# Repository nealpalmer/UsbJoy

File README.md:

# UsbJoy
USB Joystick Controller 12Digital/SmartButton, 4Analog, 1Rotary, 1NeoPixel

This is a couple of circuit boards that make up a fancy USB joystick controller for FRC #2984.
It has both a HID joystick interface and a HID uart interface (for configuration) presented to the computer (i.e. it works in Windows and Linux).  No embedded programming experience is necessary to get it to work!  It also looks like just a HID analog joystick to Windows.

To add to this readme+files:
- mechanical drawing of the board (wid, hei, hole locations)
- photo of driver's panel
- update code when I'm done fiddling with stuff
- Add pictures where appropriate (pickit programming, USB programming cable)
- A description of how to get feedback from the robot to the leds.  Does this require a networktables application?  Or use Force-Feedback mechanisms?

# Features:
- 12 Digital inputs for buttons (3-pin White/Yellow/Green JST XH: 5V, signal with 10k pullup, GND)
  - 12 is probably enough buttons for a FRC operator panel.  We use 2x of these on the operator panel, and 1 on the driver panel.
  - simple buttons and switches can be used, just connect to the 'signal' and 'GND' pins of the 3-pin connector, and ignore the '5V' pin.
- 4 Analog inputs for joysticks or linear/rotary potentiometers (10k ohms) (3-pin Blue JST XH: 5V, signal with 100k+100k pullup+pulldown, GND).
  - 1 Analog [joystick](https://www.amazon.com/dp/B08CGYGMJL) for driving (X & Y)
  - 2 [linear potentiometers](https://www.amazon.com/dp/B07HNY7VWC) are useful for controlling speeds or small adjustments to some positioning
  - There are more analog input pins that could be used for more analog inputs, but that is left upto the user to figure out if they care.  But it is probably simpler/cheaper just to make more of these boards.
- 1 Digital input can be used to drive a NeoPixel string (be careful of 500mA fuse) (3-pin Yellow)
  - Can mimic the robots LEDs (in case you can't see the robot)
  - Can give you feedback as to some positioning (i.e. target is to the left/right or up/down, and by how much)
  - Can give you feedback as to if you are holding the playing piece.
- 4-pin JST XH rotary encoder for Z-axis (600 ppr*4phase = 2400/rev resolution assumed)
  - We use the rotary encoder to control the angle that the robot is pointing on the field.  Turn the rotary knob by 5degrees, and the robot also turns by 5degrees...
- 4or5 extra 'virtual' buttons, 1 toggling (optional), 4 as constants
  - 4 virtual constant buttons make it possible to distinguish between multiple controllers easily.
  - Multiple UsbJoy boards can be distinguished from each other from the FRC Robot software (just use those constant buttons).  This means we don't have to re-arrange the joystick order in driver station.
- Arduino Pro Micro USB-C 5V ATmega32U4 controller board used for ease of soldering.
  - Make sure to get one with the fuse on the TOP side of the board (i.e. no bottom side components).  [amazon.com](https://www.amazon.com/gp/product/B0B6HYLC44)
- SmartButton support for all 12 Digital inputs
  - You can choose what each button's LED looks like for informational purposes.
  - Flickering the button when initially pressed is simple feedback that the button should be working (commuincation to UsbJoy, LED works, button works, cable connected appropriately).
  - Having the button light up when it should be useable is useful (i.e. the playing piece is being held, you can now press the shoot button).
  - Have a couple of buttons light up to indicate the state of the robot.
- 4 Digital connectors (Green) can have their 5V power switched on/off for use with simple led outputs (SmartButton requires it to always be powered on).
  - This sounded like a great idea initially, but I don't see a use for it now...
- ESD diodes on all 16 3-pin connectors
- Configuration of SmartButton settings done through the USB-UART interface.
  - Some settings are saved in EEPROM (Neopixel length, LED starting value, joystick invert axis, ...) , some are temporary (LED current values, neopixel pattern).
  - The settings are stored in the UsbJoy's EEPROM, and are configured for that particular port.  The settings aren't saved in the SmartButton itself.
  - You could compile different firmware for each button, and fix each button's LED functionality that way.
- Programming of PIC micro-controller done over USB-UART with MCLRn button press required (don't have anything plugged into J8, J11, J12).
- Programming of SmartButton PIC micro-controller over USB-UART (use a custom cable from J8+J11+J12 to SmartButton 5-pin header).
- Colored JST-XH 3-pin connectors are available on [aliexpress.com](https://www.aliexpress.us/item/3256806937445015.html)
- Colored JST-XH terminal 3-pin connectors are available on [aliexpress.com](https://www.aliexpress.us/item/3256804014172692.html)
- pre-crimped 3-pin cables are available on [aliexpress.com](https://www.aliexpress.us/item/3256807213104605.html)  Just be aware that the pins have to be removed, and swapped so that it is a 1:1 cable instead of a 1:3 cable (or you are going to connect GND to 5V, and destroy your SmartButtons).
- pre-crimped 10-pin cables are available on [amazon.com](https://www.amazon.com/dp/B0B2RCW5JF) And you would have to replace the connectors with a 3-pin version (cheap, and comes from US, so comes quickly).

# UsbJoy Connector description
- 
- J1-J12 are the button inputs.  Pin 1: 5V (square pad), Pin 2: 'signal' (short to GND during button press), Pin 3: GND.
- J7-J10 (Green connectors) can have their 5V pin switched on/off if you want to use an LED directly connected instead of a SmartButton.  They have a 100ohm series resistor for the 5V output to limit it to about 25mA (plenty for a SmartButton).
- J12 can be setup to drive a neopixel string (a programmable strip of RGB leds).  Be aware that the max current for the string should be about 400mA, any higher and the 500mA USB fuse on the Pro Micro is likely to blow.  So for very long strings, external power should be provided for the array.
- J13-J16 are the analog inputs.  Pin 1: 5V, Pin 2: analog signal, Pin 3: GND.
- J17 is the encoder input.  Pin 1: 5V (square pad), Pin 2,3: A&B encoder inputs, Pin 4: GND.  Any AB encoder can be used.  The firmware is setup to make a reasonable output for a 600 pulse/revolution=2400 change/revolution encoder (i.e. Z-axis has a range of 0-2399).  You can change the 2400 limit to any other number in the code for both the Arduino and PIC to make a different resolution encoder look right.
- J8, J11, J12 are used for PIC programming (both the UsbJoy and SmartButton PIC).
- Button between J17 and J5 is the PIC MCLRn button that connects J8.signal to MCLRn so that it is possible to program the PIC.
- J18 (5-pin holes on back side) is the PIC ICSP header.  Connect the PICKIT5 here.  You must disconnect PICKIT5 for normal operation.

# Rotary Encoder
- Uses a simple 4-pin {5V,A,B,GND} [encoder](https://www.amazon.com/dp/B01MZ4V1XP)
- 600pulses/revolution * 4 edges per pulse = 2400 positions/revolution (about 1/6degree resolution)
- Returns 0-2399 as the Z-axis to the Joystick HID interface.

# SmartButton features
- About $1 for circuit board+cpu+connector.  About $2 per illuminated arcade button.
- Designed to solder directly to 30mm illuminated arcade buttons. [amazon EG-Starts Illuminated 30mm](https://www.amazon.com/EG-STARTS-Illuminated-Buttons-Raspberry/dp/B01N11BDX9) [Aliexpress 30mm](https://www.aliexpress.us/item/3256804217382377.html) [Coin/1P/2P](https://www.aliexpress.us/item/2251832825468632.html) [AutoRGB](https://www.aliexpress.us/item/3256805580977933.html) [50pack 28mm](https://www.aliexpress.us/item/3256805775007172.html) [Free ship $10](https://www.aliexpress.us/item/2251832849688596.html)
- NOTE: 24mm illuminated buttons don't work, the pins are too close together and the button binds when the board is connected (unless you pre-bend the pins).  And they are only 1mm smaller diameter for the nut, so no reason to use them.
- Other buttons could be used.  Just solder the switch pins to the button, and the LED pins to an LED+Resistor.
- 3-pin interface (5V, signal, GND)
- Some solder jumpers can be filled, and some jumpers cut to turn a smart button into a dumb button (i.e. no 5V present).
- State of the led_option is stored in UsbJoy, and associated with the port.  So the buttons don't have to store their operational state.
- Programming of pic16f15213 can be done with either PicKit5 or UsbJoy.
- LED options
  - 0: OFF
  - 1: ON
  - 2: ON for 100ms when button gets pressed
  - 3: ON while button is pressed
  - 4: FLASHING 100ms on/100ms off
  - 5: SIN()
  - 6: FLASHING while button is pressed
  - 7: Button toggles state each time it is pressed: LED lit when in 'pressed' state
  - 8: Button toggles state each time it is pressed: LED flashes when in 'pressed' state
  - 9: you can add more if you want...

# NeoPixel
- Uses an off-the-shelf neopixel array (WS2812B 5V leds) [Strip_of_leds](https://www.amazon.com/dp/B09PBHJG6G) [ring_of_leds](https://www.amazon.com/dp/B08GPWVD57)
- Takes over Digital input #11 (the Yellow connector)
- You are going to have to make a cable that has the JST XH connector on the end of it.
- You MUST pay attention to the current draw of the string.  The entire UsbJoy is limited to 500mA, and if you draw much more than that, the fuse will blow, and everything will stop working.  So make sure that the length of string can't draw too much power.
- Possibly add an external power connection to power the neopixel array.
- Color choices:
  - 0x00-0x3f: Black-to-White solid color choices (4 values per R,G,B)
  - 0x80-0xff: Single white LED on (can be set to match the rotary encoder)
  - Rainbow
  - Moving Rainbow

# Files included:
- UsbJoy_d12_a4_r-rev2/: Kicad layout files, and gerbers
- SmartButton-rev2/: Kicad layout files, and gerbers
- UsbJoy_bill_of_materials.csv: spreadsheets with all of the parts to purchase and quantities and ordering links, pcb, buttons, cables, other stuff...
- mechanics/: openscad & STL files for a couple of mounts for UsbJoy using the SmartButton, rotary dial, 
- software/SmartButton_firmware/:
- software/UsbJoy_firmware/: firmware for the Atmega32U4 microcontroller
- software/UsbJoy_pic_firmware/: firmware 
- software/program_pic/: small application to program the pic16f1778 on UsbJoy, and pic15f15213 on SmartButton

# Manufacturing suggestions:
- [oshpark.com](https://oshpark.com/) has wonderful pricing for qty3 of 2and4 layer boards and ships in 10 calendar days for almost everything (and you can pay more to get it earlier, or pay for faster shipping)
  - [UsbJoy_R2](https://oshpark.com/shared_projects/QPZCB1ZT) board order $20/3 boards
  - [SmartButton_R2](https://oshpark.com/shared_projects/OV1uAkH7) board order $1.70/3 boards ($6.80/12 boards)
- A 3d-printer can make the UsbJoy board attach directly to the screw threads of one of the buttons.  A couple of sample mount's source files are [here](https://makerworld.com/en/models/1602536-usbjoy-controller-mount-30mm-arcade-button).
- An 3d printed [encoder spring](https://makerworld.com/en/models/1602721-rotary-encoder-rotary-friction-spring) makes the encoder much better for not spinning the robot wildly.
- An [acrylic wheel](https://makerworld.com/en/models/1605249-encoder-finger-wheel) with finger holes for the encoder is very useful.
- Testing for button functionality can be done in windows with the built-in "USB game controllers"->properties window to see the buttons that get pressed. NEED A PICTURE HERE!
- You can extract a 3d model of the boards from kicad to use in your 3d cad system.  Kicad: File->Export->STEP
- digikey has all of the electrical components necessary (except for the LED and Arduino board).
- 3x UsbJoy parts kit
- 12x SmartButton parts kit
- The arduino pro micro has a 0.5A fuse on it.  The bottom side of the board will NOT be accessible.  If that 0.5A fuse is on the bottom side, and you have over current, then your boards will not be salvageable.  So get a version that has all the components on the top side.
- The discrete components are 0603 packages for easier soldering.
- Get some [illuminated magnifying glasses](https://www.amazon.com/YOCTOSUN-Magnifying-Rechargeable-1-5X-3-5X-Magnifier/dp/B0D8J3TYL3) for ease of soldering of small components. 
- Solder all of the SMT components before any thru-hole components.  Required for both boards, because some of the thru-hole soldering will make SMT parts unreachable.

# How to program Arduino Pro Micro's Atmega32U4 (the USB device):
- Run the [Arduino GUI](https://www.arduino.cc/en/software/) version 1.8.19 (or newer than May 2025).
- Load the *.ino file
- Set up the board to be "Arduino Leonardo".
- Plug in the board into USB, then select the right Com port in the Arduino GUI.
- "Upload" 
 from the Arduino GUI.
- Programming does not clear the EEPROM, so any settings should remain unaffected.

# How to program pic16f1778 on UsbJoy using PICKIT5 programmer:
- Disconnect the last 2 buttons (Yellow and white next to each other)
- type "q1" on the uart to disable the 7,10,11 button communications
- Run the [Microchip IDE](https://www.microchip.com/en-us/tools-resources/develop/mplab-x-ide)
- Load the project
- Compile the project for production
- Use one of the current PIC programmers (pickit5 is probably preferred), and plug it into the 5-pin holes on the bottom side of the board.  And have the IDE program the device.
- type "q0" on the uart to re-enable the last 2 button functionality
# How to program pic16f1778 on UsbJoy using UsbJoy's USB connection:
- Disconnect buttons 7,10,11 (Green, White, Yellow) - they will interfere with the programming.
- Connect UsbJoy to the Windows PC.
- Figure out what com port (use Windows Device Manager) UsbJoy is using.
- Run "program_pic.exe usbjoy [filename].hex COM[#]"
- Press and hold the button next to the rotary connector for the full programming time (about 15 seconds).  If you forget this step, then you will receive a message "Error: couldn't find expected PIC CPU".
- Wait for programming to complete.
- Release the button.
- You can now reconnect the disconnected buttons.

# How to program pic16f15213 on SmartButton using PICKIT5:
- Run the [Microchip IDE](https://www.microchip.com/en-us/tools-resources/develop/mplab-x-ide)
- Load the project
- Compile the project for production
- Make sure the SmartButton isn't pressed, Connect the 3-pin cable to the UsbJoy (for 5V power), plug the pickit5 into the 5-pin holes on the SmartButton board.  And have the IDE program the device.
# How to program pic16f15213 on SmartButton using UsbJoy's USB interface:
- Connect 3+3+3pin cable ends into UsbJoy (match yellow J12,white J11,green J8 connectors), connect 5-pin cable end into SmartButton.
- Run "program_pic sb smartbutton.hex COM[#]".
- Quick Test: While plugged into the 5-pin cable, you should see the led in the button flicker VERY VERY dim.
- Quick Test: While plugged into the 5-pin cable, if you press the button, the LED should light up.
- You will need to create a cable to connect J8,J11,J12 to a 5-pin header.  It is probably easiest and more reliable to make an 3+3+3-pin to 5-pin XH only cable, and then solder the B5B-XH header to a 0.1" header.
 - pin1: MCLRn -> Red/Green/J8.2
 - pin2: 5V -> White/White/J11.1
 - pin3: GND -> Blue/Yellow/J12.3
 - pin4: PGD -> Blue/Yellow/J12.2
 - pin5: PGC -> White/White/J11.2
 - 
 - 

# How to initially configure UsbJoy:
- Connect USB to a PC.
- Open a terminal program (I like [MobaXterm](https://mobaxterm.mobatek.net/)), and connect to the correct com port (use windows device manager, and find the 'leonardo' port listed) (linux: 'dmesg' to find the correct '/dev/ttyUSB#' when you plug into USB).
- Any baud rate is fine, because it is a virtual serial port.
- 'h'+enter to get the help menu
- All settings commands are "letter+hex_number+enter".
- Important EEPROM settings to run:
  - 'u#" to set the upper 4 bits for the virtual buttons to uniquely identify this particular board (saved to EEPROM)
  - "m#val" to set the SmartLed DEFAULT setting for that port (not for the SmartLed itself) to the desired LED pattern (and toggle functionality) (saved to EEPROM)
  - "n#" to set the number of neopixel leds in the string - set to "n0" to indicate that there isn't a neopixel string.
  - "v#" to set the power-on setting for the Green ports - probably want them always on "vF" unless they are being used in some interesting way.
  - "V#" to set the power-on DEFAULT for the Green ports (saved to EEPROM)

# Future enhancements
- Add a 5-pin direct programming header for connecting to SmartButton (no need for weird programming cable).
- Move QR code to top side of board.
- UsbJoy Rev3: 4-pin header, 1 button signal, 1 led signal, no CPU on button side for LED functionality.  Still compatible with smart buttons after making a 4-pin to 3-pin cable.
- Dumbutton30mm: 4-pin header - nothing else (no cap, no res, no CPU).

# History of major changes
- 10/1/2025: Added an option for dumb buttons - fixes contention on the signal pin, and fixes spurious phantom button presses when using simple buttons.
- 8/8/2025: Added RZ axis to have the full resolution of the 2400/rev encoder when used with FRC DriverStation that only has 200 values per axis.
- 7/16/2025: Added MPLAB project files.
- 7/16/2025: SmartButton pic programming working over USB
- 7/16/2025: Added PDF of schematics.
- 7/15/2025: Uploaded 3d and lasercut objects to makerworld.com

Neal Palmer,
**FRC team #2984 Vikings Robotics,**
La Jolla, CA, USA

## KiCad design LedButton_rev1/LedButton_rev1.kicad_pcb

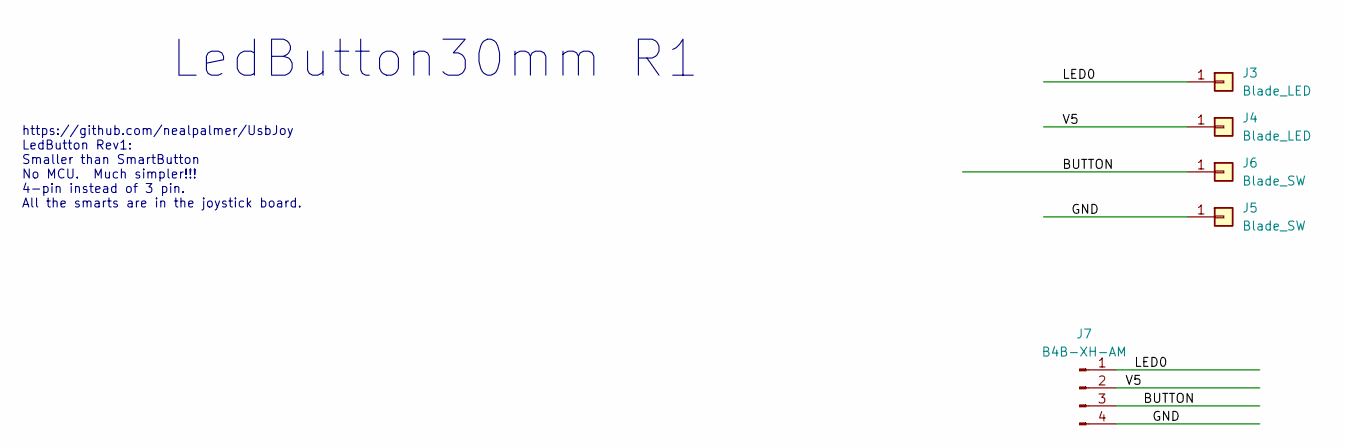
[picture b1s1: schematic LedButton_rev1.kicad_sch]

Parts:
J3, J4: Blade_LED; blade_3.75x1
J5, J6: Blade_SW; blade_3.75x1
J7: B4B-XH-AM; JST_XH_B4B-XH-AM_1x04_P2.50mm_Vertical

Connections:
/BUTTON: J6.1, J7.3
/GND: J5.1, J7.4
/LED0: J3.1, J7.1
/V5: J4.1, J7.2

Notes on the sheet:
https://github.com/nealpalmer/UsbJoy LedButton Rev1: Smaller than SmartButton No MCU. Much simpler!!! 4-pin instead of 3 pin. All the smarts are in the joystick board.
LedButton30mm R1

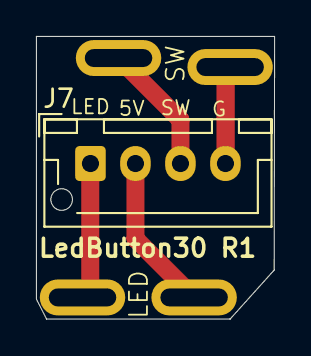
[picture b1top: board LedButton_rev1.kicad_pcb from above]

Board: 2 copper layers, 13.2 x 15.7 mm, 5 parts (0 on the bottom side), 4 nets.

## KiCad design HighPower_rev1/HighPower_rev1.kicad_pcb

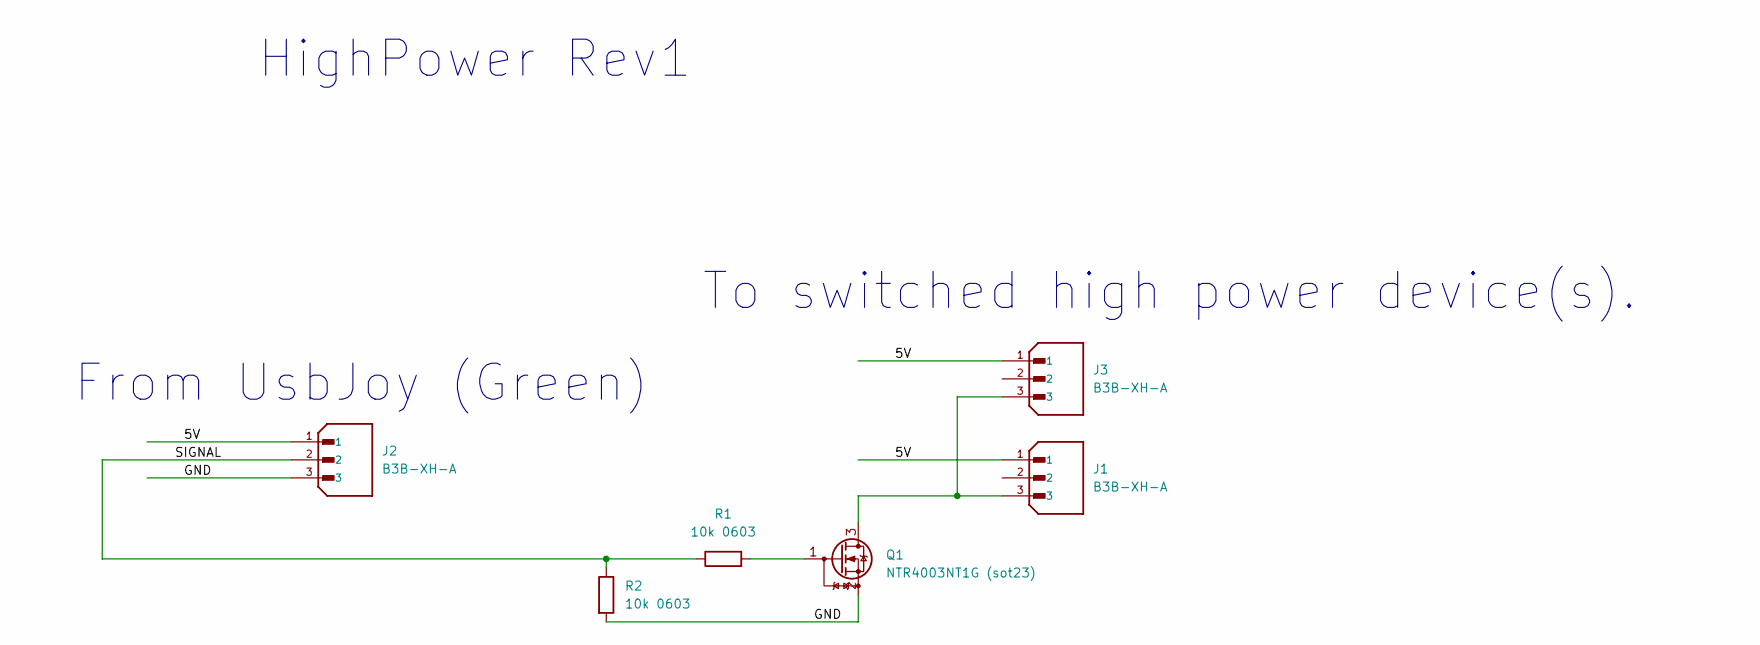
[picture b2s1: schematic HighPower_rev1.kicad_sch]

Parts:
J1, J2, J3: B3B-XH-A; JST_XH_B3B-XH-A_1x03_P2.50mm_Vertical; PARTREV 7/4/21
Q1: NTR4003NT1G (sot23); SOT-23
R1, R2: 10k 0603; C_0603_1608Metric_Pad1.08x0.95mm_HandSolder

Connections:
/5V: J1.1, J2.1, J3.1
/GND: J2.3, Q1.2 (S), R2.2
/SIGNAL: J2.2, R1.1, R2.1
unnamed: J1.3, J3.3, Q1.3 (D)
unnamed: Q1.1 (G), R1.2

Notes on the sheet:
HighPower Rev1
From UsbJoy (Green)
To switched high power device(s).

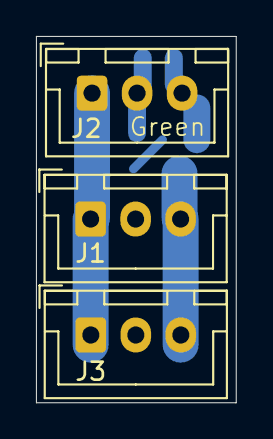
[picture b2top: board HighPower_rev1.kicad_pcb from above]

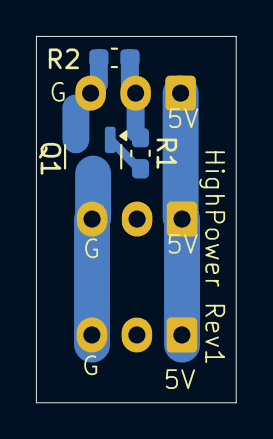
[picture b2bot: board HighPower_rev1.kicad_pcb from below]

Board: 2 copper layers, 11.1 x 20.4 mm, 6 parts (3 on the bottom side), 5 nets.

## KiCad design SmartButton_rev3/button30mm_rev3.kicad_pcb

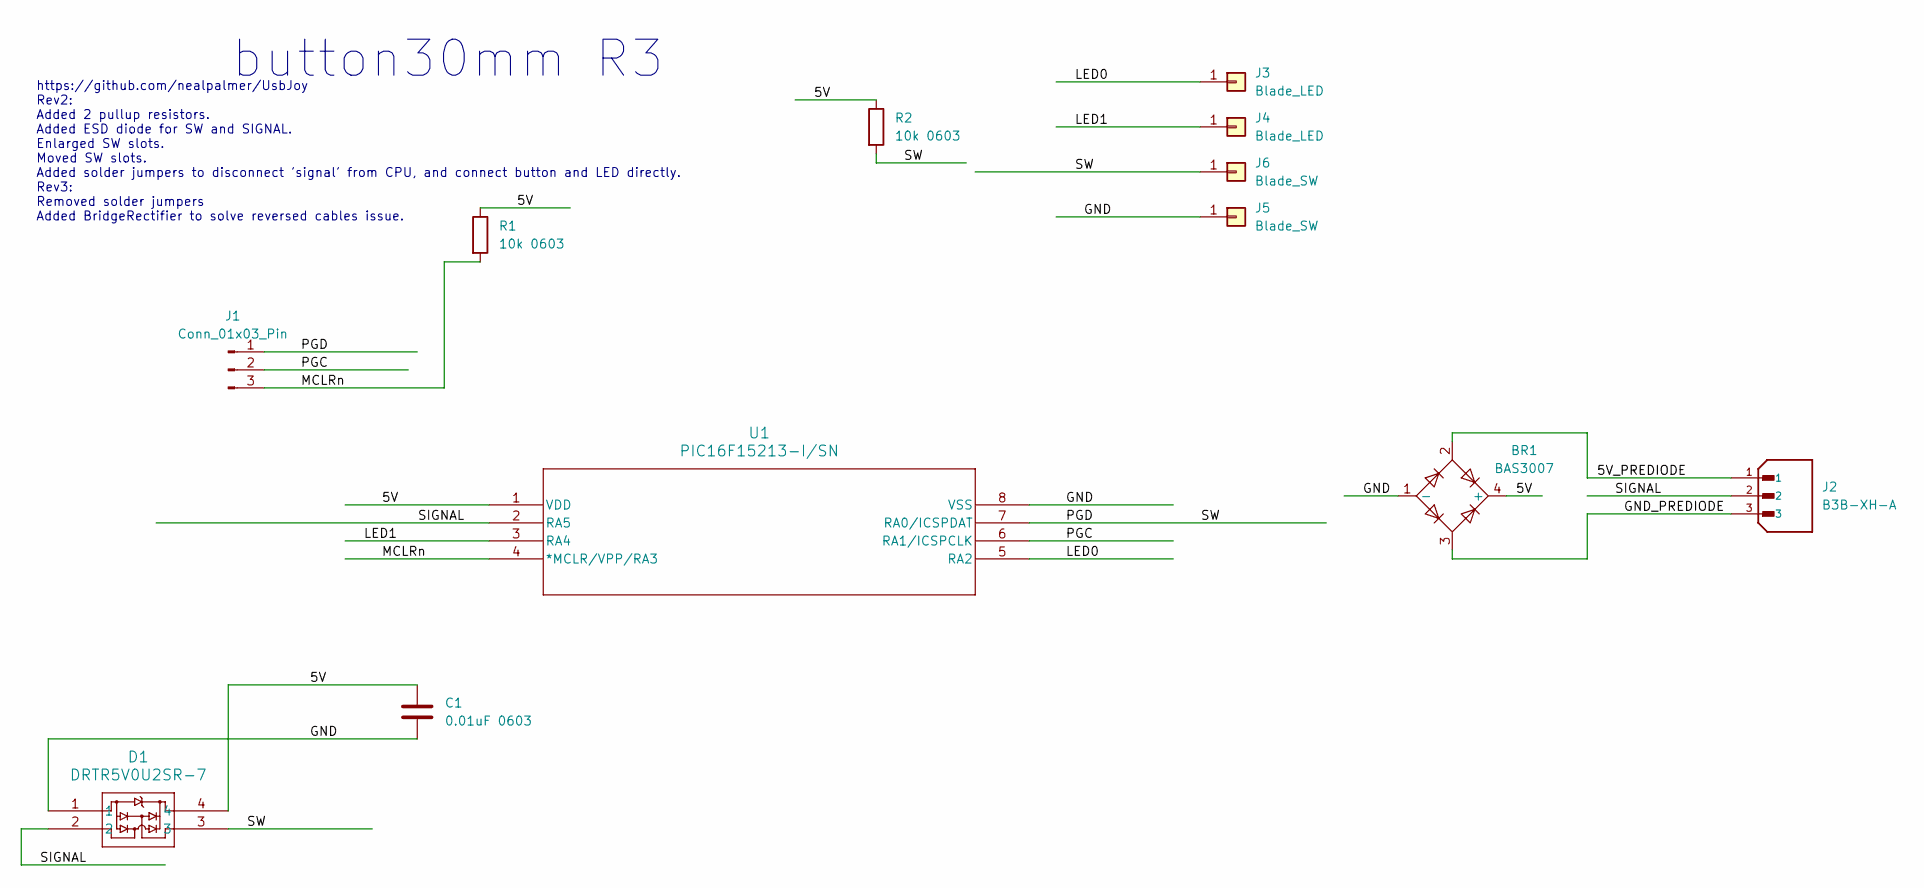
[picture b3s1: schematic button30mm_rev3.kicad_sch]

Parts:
BR1: BAS3007; SOT143_DIO
C1: 0.01uF 0603; C_0603_1608Metric_Pad1.08x0.95mm_HandSolder
D1: DRTR5V0U2SR-7; SOT143_DIO
J1: Conn_01x03_Pin; PinHeader_1x03_P2.54mm_Vertical
J2: B3B-XH-A; JST_XH_B3B-XH-A_1x03_P2.50mm_Vertical; PARTREV 7/4/21
J3, J4: Blade_LED; blade_3.75x1
J5, J6: Blade_SW; blade_3.75x1
R1, R2: 10k 0603; C_0603_1608Metric_Pad1.08x0.95mm_HandSolder
U1: PIC16F15213-I/SN; SOIC-8_3.9x4.9mm_P1.27mm

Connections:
/5V: BR1.4 (+), C1.1, D1.4, R1.1, R2.1, U1.1 (VDD)
/5V_PREDIODE: BR1.2, J2.1
/GND: BR1.1 (-), C1.2, D1.1, J5.1, U1.8 (VSS)
/GND_PREDIODE: BR1.3, J2.3
/LED0: J3.1, U1.5 (RA2)
/LED1: J4.1, U1.3 (RA4)
/MCLRn: J1.3, R1.2, U1.4 (*MCLR/VPP/RA3)
/PGC: J1.2, U1.6 (RA1/ICSPCLK)
/PGD: D1.3, J1.1, J6.1, R2.2, U1.7 (RA0/ICSPDAT)
/SIGNAL: D1.2, J2.2, U1.2 (RA5)

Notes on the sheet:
https://github.com/nealpalmer/UsbJoy Rev2: Added 2 pullup resistors. Added ESD diode for SW and SIGNAL. Enlarged SW slots. Moved SW slots. Added solder jumpers to disconnect 'signal' from CPU, and connect button and LED directly. Rev3: Removed solder jumpers Added BridgeRectifier to solve reversed 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
button30mm R3

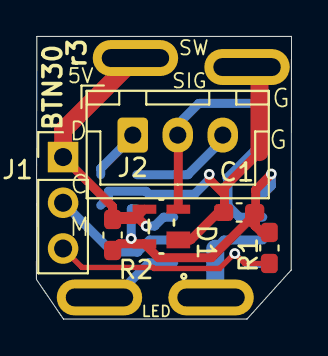
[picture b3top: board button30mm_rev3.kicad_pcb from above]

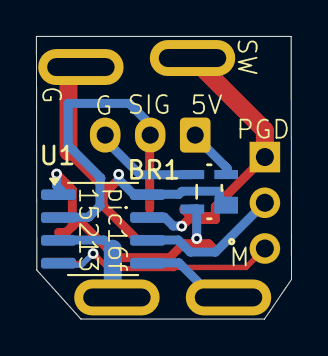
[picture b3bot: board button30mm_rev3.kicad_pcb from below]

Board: 2 copper layers, 14.2 x 15.7 mm, 12 parts (2 on the bottom side), 10 nets.

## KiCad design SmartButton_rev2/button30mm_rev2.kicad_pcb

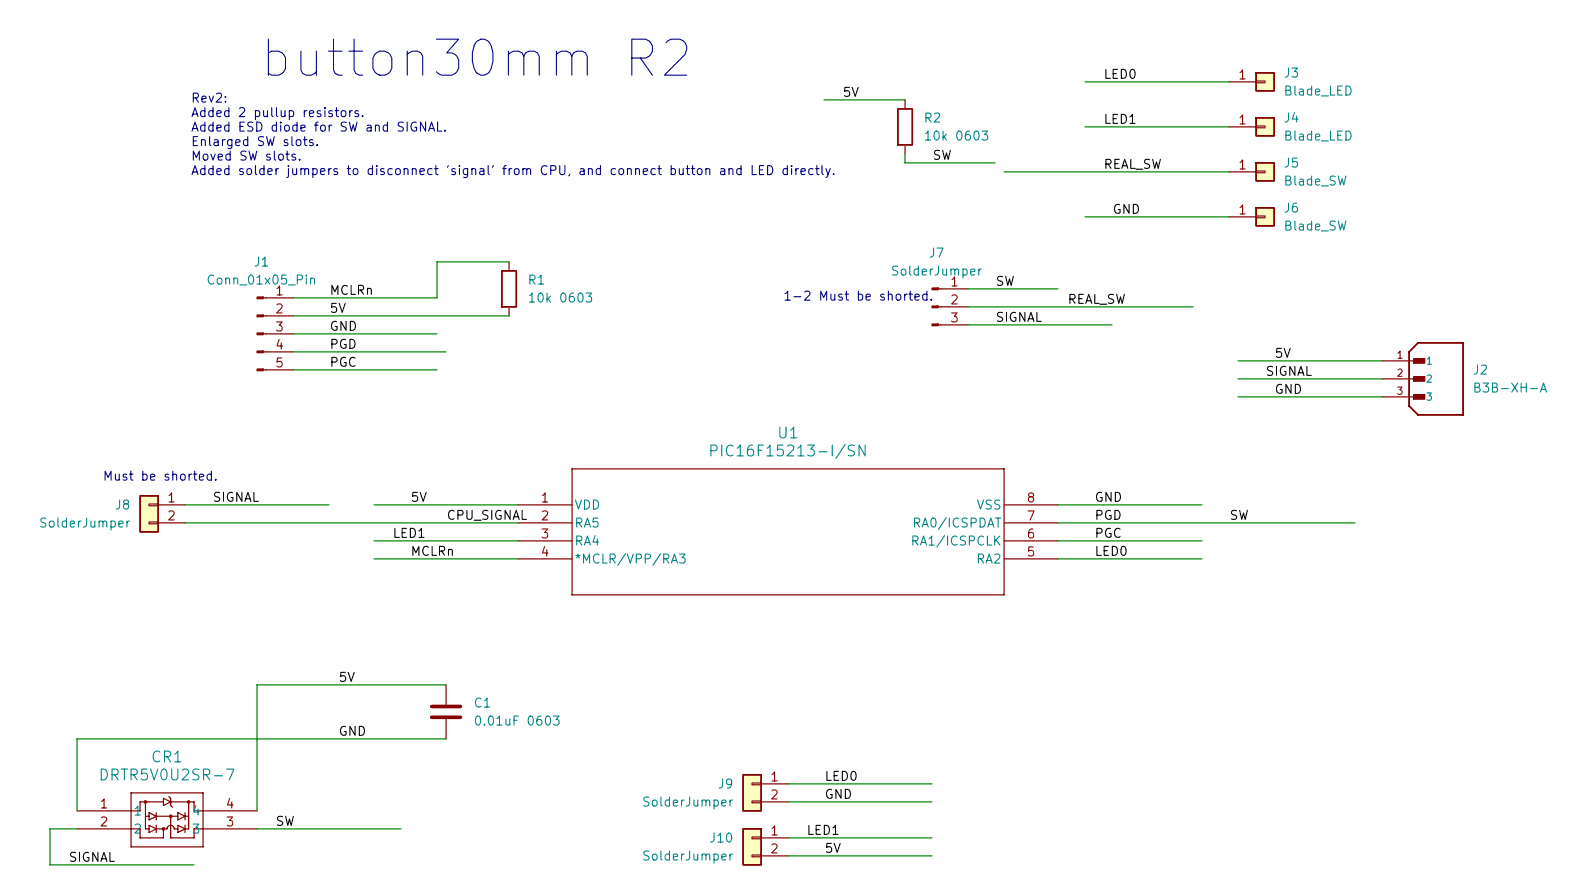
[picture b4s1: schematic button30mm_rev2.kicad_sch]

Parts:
C1: 0.01uF 0603; C_0603_1608Metric_Pad1.08x0.95mm_HandSolder
CR1: DRTR5V0U2SR-7; SOT143_DIO
J1: Conn_01x05_Pin; PinHeader_1x05_P2.54mm_Vertical
J2: B3B-XH-A; JST_XH_B3B-XH-A_1x03_P2.50mm_Vertical; PARTREV 7/4/21
J3, J4: Blade_LED; blade_3.75x1
J5, J6: Blade_SW; blade_3.75x1
J7: SolderJumper; SolderJumper-3_P1.3mm_Shorted_Pad0.8x0.4mm
J8: SolderJumper; SolderJumper-2_P1.3mm_Shorted_Pad0.4x0.8mm
J9, J10: SolderJumper; SolderJumper-2_P1.3mm_Open_Pad0.4x0.8mm
R1, R2: 10k 0603; C_0603_1608Metric_Pad1.08x0.95mm_HandSolder
U1: PIC16F15213-I/SN; SOIC-8_5.3x5.3mm_P1.27mm

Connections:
/5V: C1.1, CR1.4, J1.2, J2.1, J10.2, R1.2, R2.1, U1.1 (VDD)
/CPU_SIGNAL: J8.2, U1.2 (RA5)
/GND: C1.2, CR1.1, J1.3, J2.3, J6.1, J9.2, U1.8 (VSS)
/LED0: J3.1, J9.1, U1.5 (RA2)
/LED1: J4.1, J10.1, U1.3 (RA4)
/MCLRn: J1.1, R1.1, U1.4 (*MCLR/VPP/RA3)
/PGC: J1.5, U1.6 (RA1/ICSPCLK)
/PGD: CR1.3, J1.4, J7.1, R2.2, U1.7 (RA0/ICSPDAT)
/REAL_SW: J5.1, J7.2
/SIGNAL: CR1.2, J2.2, J7.3, J8.1

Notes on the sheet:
Must be shorted.
Rev2: Added 2 pullup resistors. Added ESD diode for SW and SIGNAL. Enlarged SW slots. Moved SW slots. Added solder jumpers to disconnect 'signal' from CPU, and connect button and LED directly.
button30mm R2
1-2 Must be shorted.

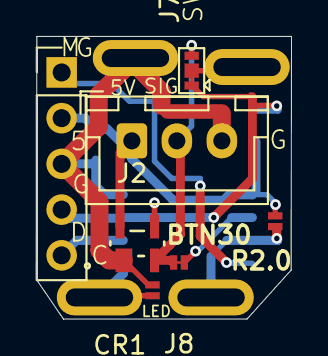
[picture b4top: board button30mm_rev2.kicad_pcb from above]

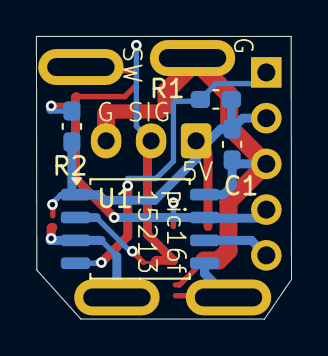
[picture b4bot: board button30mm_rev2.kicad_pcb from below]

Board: 2 copper layers, 14.2 x 15.7 mm, 15 parts (4 on the bottom side), 10 nets.

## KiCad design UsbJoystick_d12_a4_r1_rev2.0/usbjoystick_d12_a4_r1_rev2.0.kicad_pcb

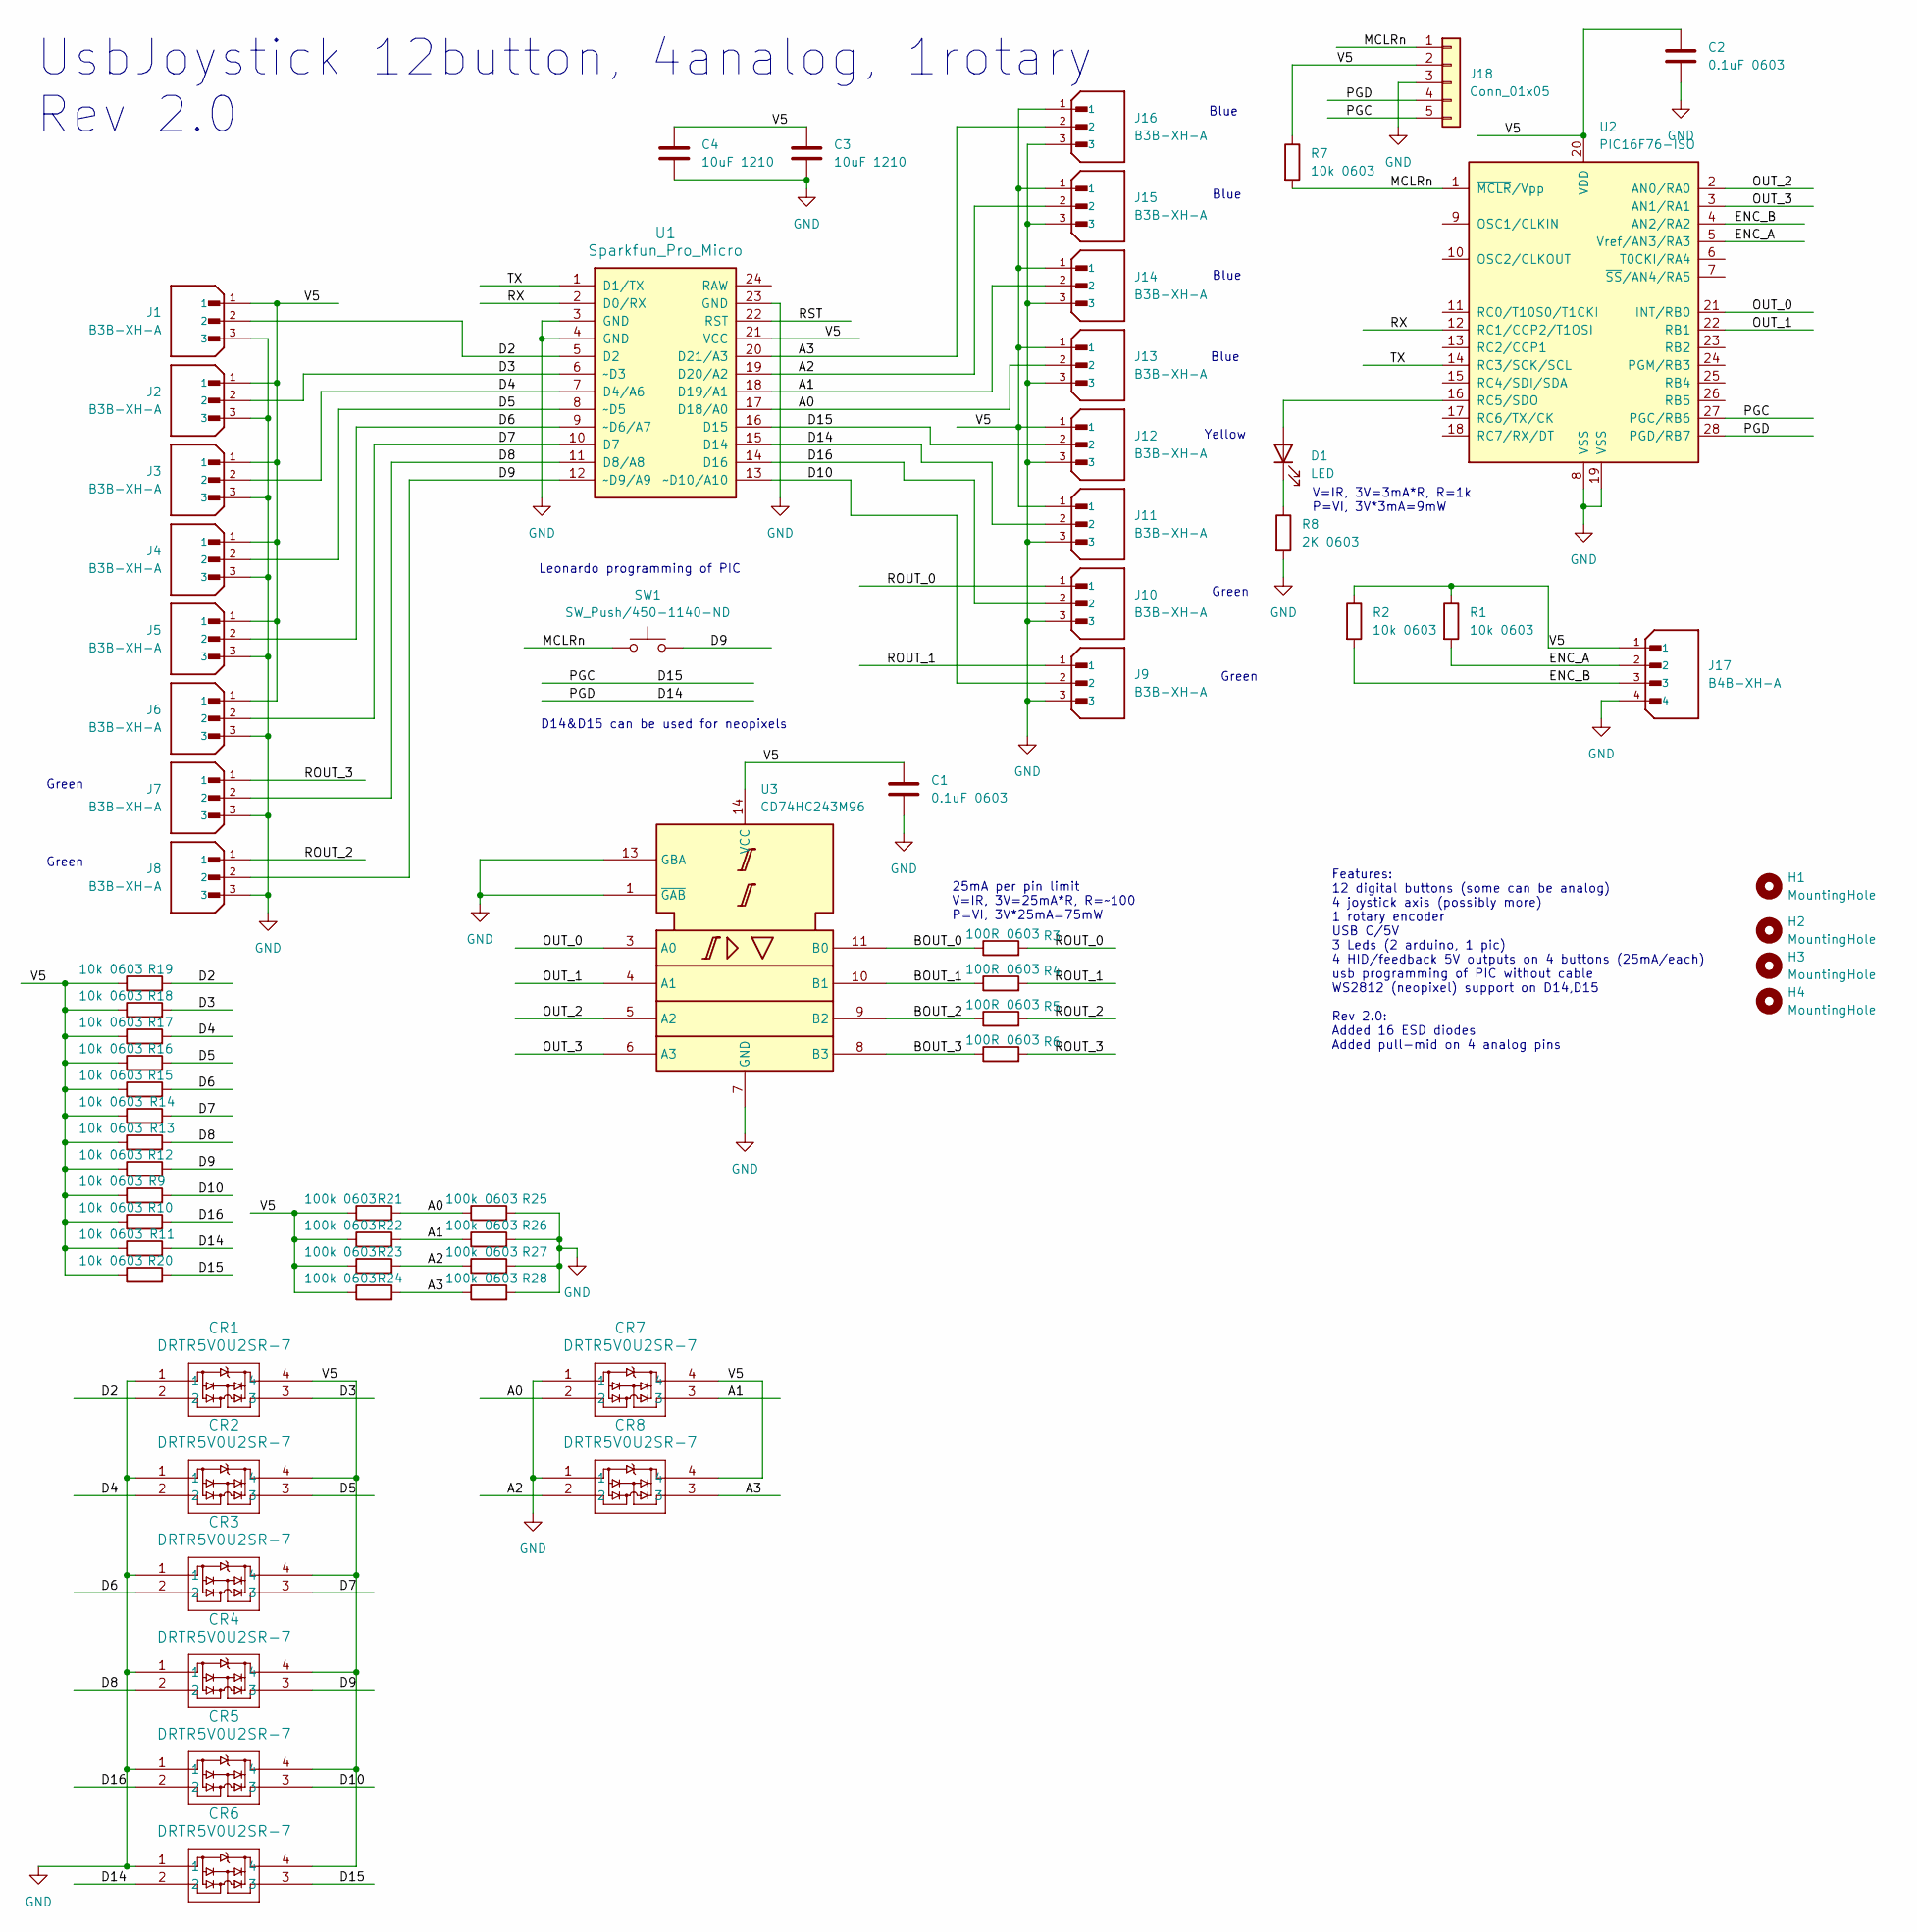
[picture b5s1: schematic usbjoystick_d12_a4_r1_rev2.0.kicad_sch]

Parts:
C1, C2: 0.1uF 0603; C_0603_1608Metric_Pad1.08x0.95mm_HandSolder
C3, C4: 10uF 1210; C_1210_3225Metric_Pad1.33x2.70mm_HandSolder
CR1, CR2, CR3, CR4, CR5, CR6, CR7, CR8: DRTR5V0U2SR-7; SOT-143_Handsoldering
D1: LED; LED_0603_1608Metric
H1, H2, H3, H4: MountingHole; MountingHole_3.2mm_M3
J1, J2, J3, J4, J5, J6, J7, J8, J9, J10, J11, J12, J13, J14, J15, J16: B3B-XH-A; JST_B3B-XH-A; PARTREV 7/4/21
J17: B4B-XH-A; JST_B4B-XH-A; PARTREV 7/4/21
J18: Conn_01x05; PinSocket_1x05_P2.54mm_Vertical
R1, R2, R7, R9, R10, R11, R12, R13, R14, R15, R16, R17, R18, R19, R20: 10k 0603; C_0603_1608Metric_Pad1.08x0.95mm_HandSolder
R3, R4, R5, R6: 100R 0603; C_0603_1608Metric_Pad1.08x0.95mm_HandSolder
R8: 2K 0603; C_0603_1608Metric_Pad1.08x0.95mm_HandSolder
R21, R22, R23, R24, R25, R26, R27, R28: 100k 0603; C_0603_1608Metric_Pad1.08x0.95mm_HandSolder
SW1: SW_Push/450-1140-ND; SW_SPST_FSMSM
U1: Sparkfun_Pro_Micro
U2: PIC16F76-ISO; SOIC-28W_7.5x17.9mm_P1.27mm
U3: CD74HC243M96; SO-14_3.9x8.65mm_P1.27mm

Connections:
/A0: CR7.2, J13.2, R21.2, R25.1, U1.17 (D18/A0)
/A1: CR7.3, J14.2, R22.2, R26.1, U1.18 (D19/A1)
/A2: CR8.2, J15.2, R23.2, R27.1, U1.19 (D20/A2)
/A3: CR8.3, J16.2, R24.2, R28.1, U1.20 (D21/A3)
/BOUT_0: R3.1, U3.11 (B0)
/BOUT_1: R4.1, U3.10 (B1)
/BOUT_2: R5.1, U3.9 (B2)
/BOUT_3: R6.1, U3.8 (B3)
/D2: CR1.2, J1.2, R19.2, U1.5 (D2)
/D3: CR1.3, J2.2, R18.2, U1.6 (~D3)
/D4: CR2.2, J3.2, R17.2, U1.7 (D4/A6)
/D5: CR2.3, J4.2, R16.2, U1.8 (~D5)
/D6: CR3.2, J5.2, R15.2, U1.9 (~D6/A7)
/D7: CR3.3, J6.2, R14.2, U1.10 (D7)
/D8: CR4.2, J7.2, R13.2, U1.11 (D8/A8)
/D9: CR4.3, J8.2, R12.2, SW1.2, U1.12 (~D9/A9)
/D10: CR5.3, J9.2, R9.2, U1.13 (~D10/A10)
/D14: CR6.2, J11.2, J18.4, R11.2, U1.15 (D14), U2.28 (PGD/RB7)
/D15: CR6.3, J12.2, J18.5, R20.2, U1.16 (D15), U2.27 (PGC/RB6)
/D16: CR5.2, J10.2, R10.2, U1.14 (D16)
/ENC_A: J17.2, R1.2, U2.5 (Vref/AN3/RA3)
/ENC_B: J17.3, R2.2, U2.4 (AN2/RA2)
/MCLRn: J18.1, R7.2, SW1.1, U2.1 (~MCLR/Vpp)
/OUT_0: U2.21 (INT/RB0), U3.3 (A0)
/OUT_1: U2.22 (RB1), U3.4 (A1)
/OUT_2: U2.2 (AN0/RA0), U3.5 (A2)
/OUT_3: U2.3 (AN1/RA1), U3.6 (A3)
/ROUT_0: J10.1, R3.2
/ROUT_1: J9.1, R4.2
/ROUT_2: J8.1, R5.2
/ROUT_3: J7.1, R6.2
/RST: U1.22 (RST)
/RX: U1.2 (D0/RX), U2.12 (RC1/CCP2/T1OSI)
/TX: U1.1 (D1/TX), U2.14 (RC3/SCK/SCL)
/V5: C1.1, C2.1, C3.1, C4.1, CR1.4, CR2.4, CR3.4, CR4.4, CR5.4, CR6.4, CR7.4, CR8.4, J1.1, J2.1, J3.1, J4.1, J5.1, J6.1, J11.1, J12.1, J13.1, J14.1, J15.1, J16.1, J17.1, J18.2, R1.1, R2.1, R7.1, R9.1, R10.1, R11.1, R12.1, R13.1, R14.1, R15.1, R16.1, R17.1, R18.1, R19.1, R20.1, R21.1, R22.1, R23.1, R24.1, U1.21 (VCC), U2.20 (VDD), U3.14 (VCC)
GND: C1.2, C2.2, C3.2, C4.2, CR1.1, CR2.1, CR3.1, CR4.1, CR5.1, CR6.1, CR7.1, CR8.1, J1.3, J2.3, J3.3, J4.3, J5.3, J6.3, J7.3, J8.3, J9.3, J10.3, J11.3, J12.3, J13.3, J14.3, J15.3, J16.3, J17.4, J18.3, R8.2, R25.2, R26.2, R27.2, R28.2, U1.3 (GND), U1.4 (GND), U1.23 (GND), U2.8 (VSS), U2.19 (VSS), U3.1 (~GAB), U3.7 (GND), U3.13 (GBA)
unnamed: D1.2 (A), U2.16 (RC5/SDO)
unnamed: D1.1 (K), R8.1

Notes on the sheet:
Leonardo programming of PIC
Green
Blue
Yellow
UsbJoystick 12button, 4analog, 1rotary Rev 2.0
D14&D15 can be used for neopixels
25mA per pin limit V=IR, 3V=25mA*R, R=~100 P=VI, 3V*25mA=75mW
Features: 12 digital buttons (some can be analog) 4 joystick axis (possibly more) 1 rotary encoder USB C/5V 3 Leds (2 arduino, 1 pic) 4 HID/feedback 5V outputs on 4 buttons (25mA/each) usb programming of PIC without cable WS2812 (neopixel) support on D14,D15 Rev 2.0: Added 16 ESD diodes Added pull-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
V=IR, 3V=3mA*R, R=1k P=VI, 3V*3mA=9mW

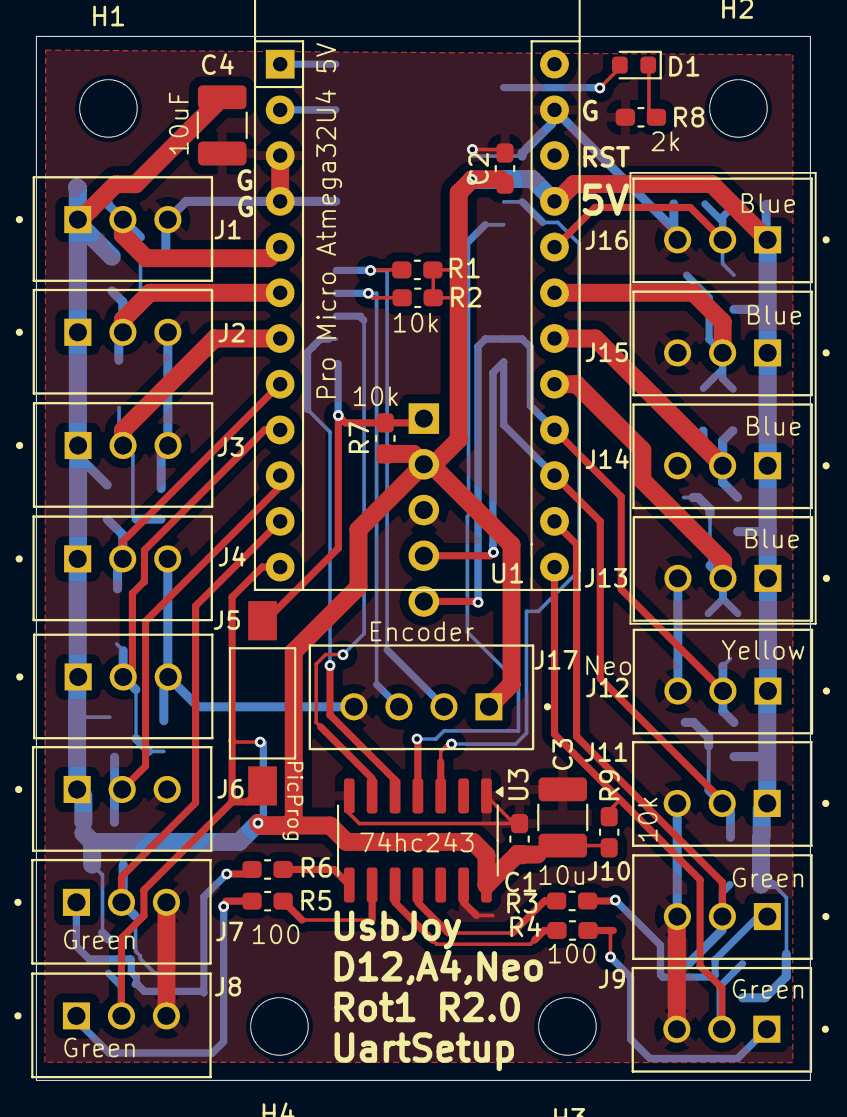
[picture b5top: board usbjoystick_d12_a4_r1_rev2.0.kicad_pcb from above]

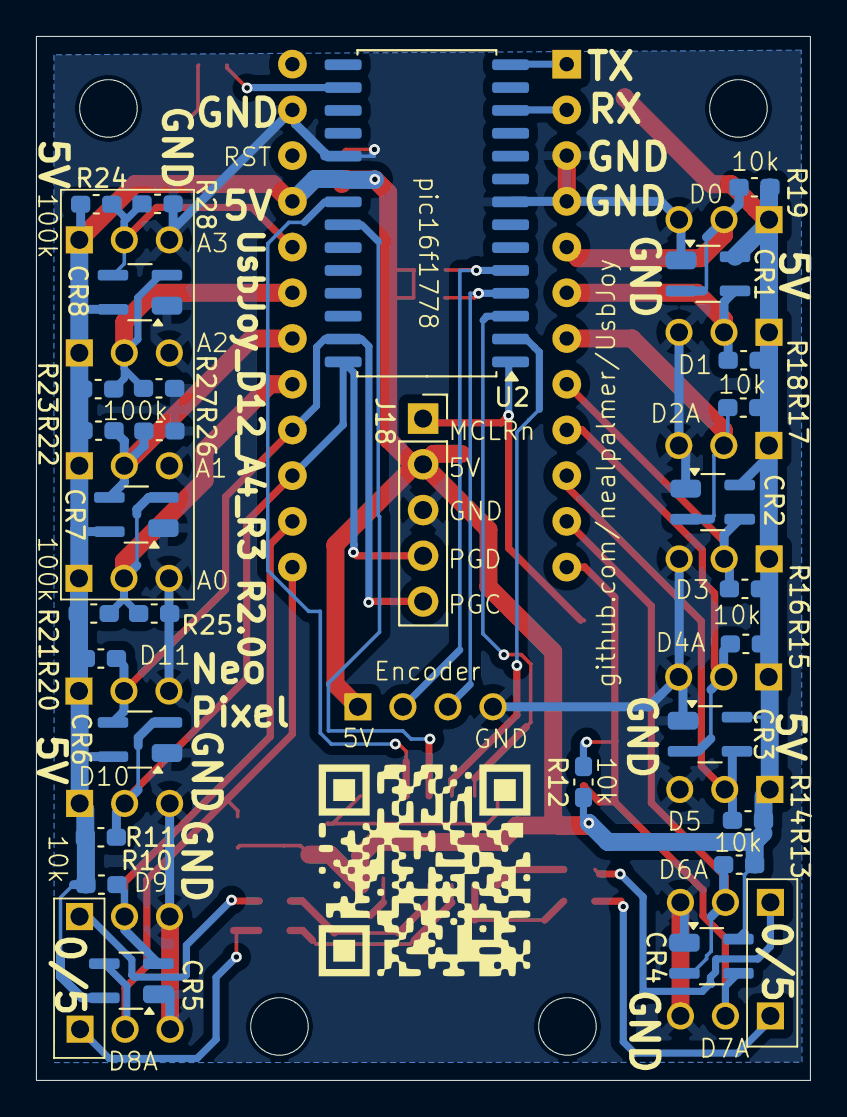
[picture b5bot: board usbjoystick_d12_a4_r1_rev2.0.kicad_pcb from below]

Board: 2 copper layers, 43.0 x 58.0 mm, 67 parts (29 on the bottom side), 37 nets.

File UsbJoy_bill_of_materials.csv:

Description,ref des,$/each,total Qty,Qty/UsbJoy,Qty/SmartButton,Qty other,Purchasing link
Oshpark UsbJoy 3x UsbJoy PCB,,$7.00,1,1,,,https://oshpark.com/shared_projects/QPZCB1ZT
Digikey kit of 3x UsbJoy parts,,,1,1,,,
Oshpark SmartButton 3x SmartButton PCB,,$0.50,1,,1,,https://oshpark.com/shared_projects/OV1uAkH7
Digikey kit of 12x SmartButton parts,,,1,,1,,
30mm illuminated arcade buttons (5x),,$2.00,1,,1,,https://www.amazon.com/dp/B01N11BDX9
,,,,,,,
600ppm encoder,,$16.99,1,,,1,https://www.amazon.com/dp/B01MZ4V1XP
encoder finger wheel,,laser cut,1,,,1,https://makerworld.com/en/models/1605249-encoder-finger-wheel
UsbJoy mount to SmartButton,,printed plastic,1,,,1,https://makerworld.com/en/models/1602536-usbjoy-controller-m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
encoder springs,,printed plastic,1,,,1,https://makerworld.com/en/models/1602721-rotary-encoder-rota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
analog joystick,,$17.89,1,,,1,https://www.amazon.com/dp/B08CGYGMJL
linear potentiometer,,$2.00,2,,,2,https://www.amazon.com/dp/B07HNY7VWC
,,,,,,,
JST XH 3-pin connector end,,,32,,,32,
JST XH crimp pins,,,96,,,96,
XH wires with 5-pin connectors (need to replace with 3-pin) (20 pieces),,$0.44,1,,,1,https://www.amazon.com/dp/B0B2RCW5JF
magnifying glasses,,$23.99,0,,,,https://www.amazon.com/Dilzekui-Magnifier-Rechargeable-Magni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
neopixel string,,$14.99,1,,,1,https://www.amazon.com/dp/B09PBHJG6G
neopixel ring,,$25.99,1,,,1,https://www.amazon.com/dp/B083VWVP3J?ref_=ppx_hzsearch_conn_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
,,,,,,,
B3B-XH-A (white JST XH 3-pin),"J1, J2, J3, J4, J5, J6, J11",,7,7,,,
B3B-XH-A (green JST XH 3-pin),"J7, J8, J9, J10",,4,4,,,
B3B-XH-A (blue JST XH 3-pin),"J13, J14, J15, J16",,4,4,,,
B3B-XH-A (yellow JST XH 3-pin),J12,,1,1,,,
B4B-XH-A (white JST XH 4-pin),J17,,1,1,,,
Pro Micro Arduino with USB-C,U1,,1,1,,,
"CD74HC243M96 (SOIC 14, 5V, buffer)",U3,,1,1,,,
"pic16f1778 (SOIC 28, 5V)",U2,,1,1,,,
Green LED 0603,D1,,1,1,,,
100k 0603 5% resistor,"R25, R26, R27, R28, R21, R22, R23, R24",,8,8,,,
10k 0603 5% resistor,"R7, R1, R2, R19, R18, R17, R16, R15, R14, R13, R12, R9, R10, R11, R20",,15,15,,,
2k 0603 5% resistor,R8,,1,1,,,
DRTR5V0U2SR-7 (esd diode),"CR1, CR2, CR3, CR4, CR5, CR6, CR7, CR8",,8,8,,,
10uF 6.3V 1210 ceramic capacitor,"C3, C4",,2,2,,,
0.1uF 6.3V 0603 ceramic capacitor,"C1, C2",,2,2,,,
450-1140-ND (momentary push button),SW1,,1,1,,,
100ohm 0603 5% resistor,"R3, R4, R5, R6",,4,4,,,
,,,0,,,,
,,,0,,,,
B3B-XH-A (white JST XH 3-pin),J2,,1,,1,,
0.01uF 0603 6.3V ceramic capacitor,C1,,1,,1,,
10k 0603 5% resistor,"R1, R2",,2,,2,,
"pic16f15213-I/SN (soic8, 5V)",U1,,1,,1,,
DRTR5V0U2SR-7 (esd diode),CR1,,1,,1,,
,,,0,,,,
,,,0,,,,
,,,0,,,,
,,,0,,,,
,,,0,,,,
,,,0,,,,
,,,0,,,,
,,,0,,,,
,,,0,,,,
,,,0,,,,
,,,0,,,,
,,,0,,,,
,,,0,,,,
,,,0,,,,

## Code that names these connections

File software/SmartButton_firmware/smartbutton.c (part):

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#pragma config BOREN = 3 // always enabled
#pragma config WDTE = 0 // always disabled
#pragma config PWRTS = 3 // always disabled
#pragma config MCLRE = 1 // MCLRn pin functionality

#pragma config LVP = 1 // low voltage programming
#pragma config WRTSAF = 1 // not write protected
#pragma config SAFEN = 0 // reserve StorageAreaFlash starting at address 0x780 for 128 words

#define signal LATA5
#define button RA0

//#define LEDA4
//#ifdef LEDA4
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		ANSELA = 0x04;
		TRISA2 = 1; // let it get pulled high
		TRISA4 = 0; // drive to GND
		ADCON0bits.CHS = 2; // RA2
	} else {
		ANSELA = 0x10;
		TRISA2 = 0; // drive to GND
		TRISA4 = 1; // let it get pulled high
		ADCON0bits.CHS = 4; // RA4
	}
	ADCON1bits.CS = 2; // Fosc/32 (32us)
	ADCON1bits.FM = 0; // result: {ADRESH[7:0], ADRESL[7:6]}
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T1GCONbits.GPOL = 0; // enable when ‘signal’ is low
T1GCONbits.GSPM = 1; // single acquisition enable
T1GATE = 0; // gate signal from from T1GPPS
T1GPPS = 5; // RA5 = ‘signal’ pin;
TMR1L = 0;
TMR1H = 0;
T1CLK = 2; // HFINTOSC (32Mhz) is clock source 
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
